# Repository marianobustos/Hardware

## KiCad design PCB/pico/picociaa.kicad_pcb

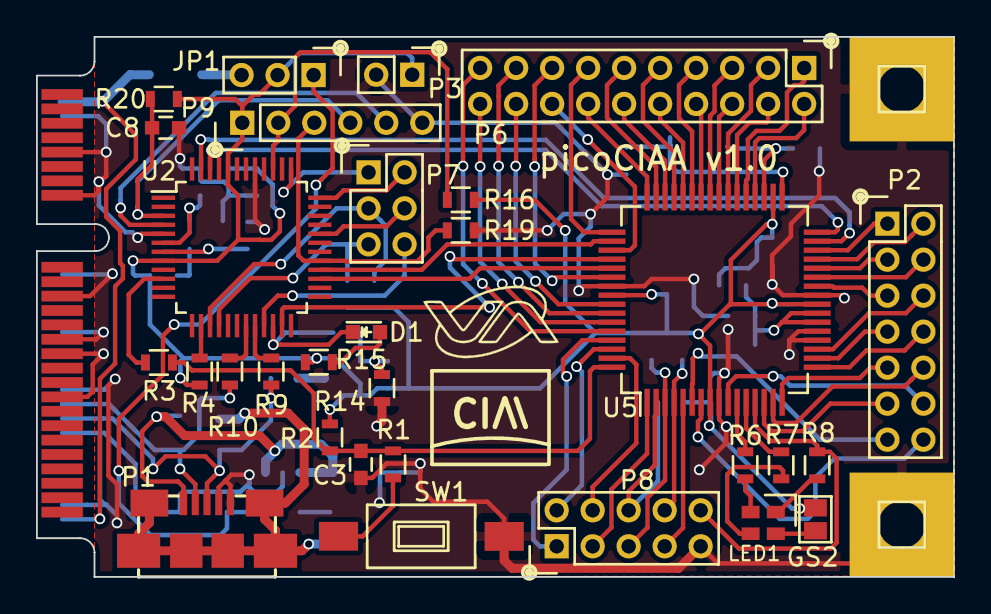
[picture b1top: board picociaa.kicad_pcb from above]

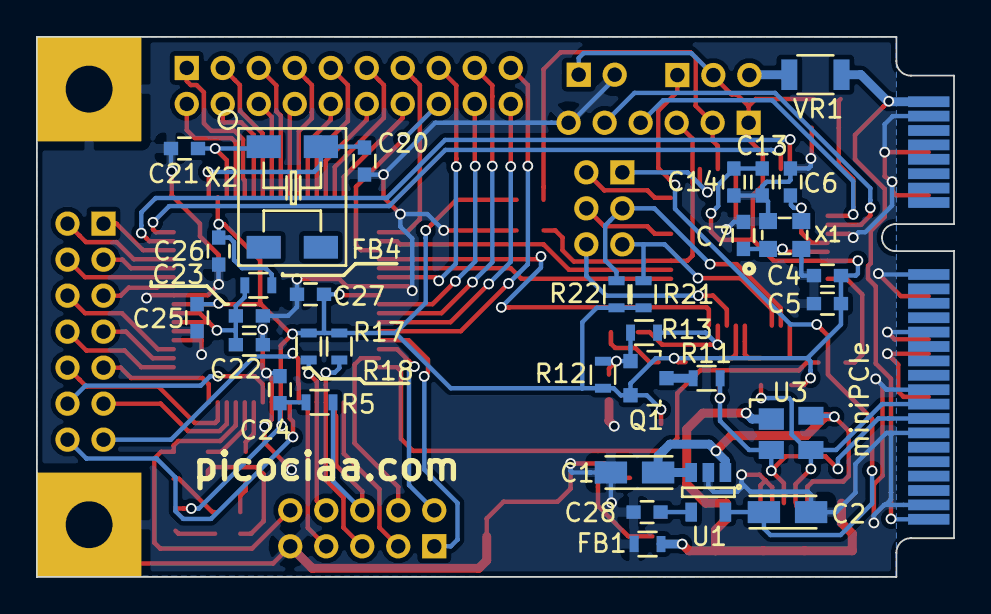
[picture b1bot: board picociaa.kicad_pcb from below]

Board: 2 copper layers, 51.0 x 30.0 mm, 66 parts (33 on the bottom side), 89 nets.

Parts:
C1, C2: 10uF; TantalC_SizeA_EIA-3216_Reflow
C3, C4, C8, C13, C23, C24, C25, C26, C27: 100nF; C_0603
C5, C14, C22, C28: 10nF; C_0603
C6, C7: 18pF; C_0603
C20, C21: 20pF; C_0603
D1: LED; LED_0603
FB1, FB4: FILTER; R_0603
GS2: GS2
J1: PCIE-MINI; miniPCIeConn
JP1: VDD Sel.; Pin_Header_Straight_1x03_Pitch2.00mm
LED1: LTST-C19FD1WT; PLCC-4
P1: ZX62D-B-5P8; USB_microAB_ZX62-AB&B-5PA-11
P2: IO2; Pin_Header_Straight_2x07_Pitch2.00mm
P3: PWR; Pin_Header_Straight_1x02_Pitch2.00mm
P4, P5: MOUNTING_HOLE; PIN_ARRAY_1
P6: IO1; Pin_Header_Straight_2x10_Pitch2.00mm
P7: DBG_IO; Pin_Header_Straight_2x03_Pitch2.00mm
P8: IO3; Pin_Header_Straight_2x05_Pitch2.00mm
P9: DBG_SWD; Pin_Header_Straight_1x06_Pitch2.00mm
Q1: BC857; SOT-23
R1, R3: 100; R_0603
R2, R5: 100k; R_0603
R4, R13, R15, R21, R22: 2k; R_0603
R6, R7: 270; R_0603
R8, R11: 1.5k; R_0603
R9, R10: 33; R_0603
R12, R16, R19: 24k; R_0603
R14: UL; R_0603
R17, R18: 2.2k; R_0603
R20: 10k; R_0603
SW1: RESET; SW_SPST_FSMSM
U1: MIC5319-3.3YD5; SOT-23-5
U2: LPC11U35FBD48; LQFP-48_7x7mm_Pitch0.5mm
U3: PRTR5V0U2X; SOT-143
U5: LPC54102J512BD64; TQFP-64_10x10mm_Pitch0.5mm
VR1: VR; R_1206
X1: 12MHz; FA238V-XTAL
X2: 32.768kHz; 4SOJ

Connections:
+3V3: C4.1, C5.1, C13.1, C14.1, C24.1, C25.1, C26.1, C27.1, FB4.2, GS2.2, JP1.2, P3.1, P9.1, Q1.2, R2.1, R4.2, R5.1, R12.1, R15.1, R16.1, R17.2, R18.2, R20.1, R21.2, R22.2, U2.8, U2.44, U5.8, U5.24, U5.34, U5.56
/CHASSIS: FB1.1, P1.6, P1.7, P1.8, P1.9, U3.1
/Debugger/DBG_SWCLK: P9.3, R19.1, U2.29
/Debugger/DBG_SWDIO: P9.2, R16.2, U2.39
/Debugger/DBG_~ISP~: P9.5, U2.4
/Debugger/DBG_~RST~: C8.1, P9.4, R20.2, U2.3
/Debugger/PIO0_4: P7.3, R22.1, U2.15
/Debugger/PIO0_5: P7.5, R21.1, U2.16
/Debugger/PIO0_11: P7.4, U2.32
/Debugger/PIO1_13: P7.2, U2.36
/Debugger/PIO1_14: P7.1, U2.37
/Debugger/PIO1_24: P7.6, U2.21
/Debugger/TGT_TXD: U2.46, U5.32
/Debugger/TGT_~RESET~: C3.1, R1.2, R2.2, R3.2, U5.64
/Debugger/USB_N: J1.36, P1.2, R10.1, U3.3
/Debugger/USB_P: J1.38, P1.3, R9.1, R11.1, U3.2
/Debugger/~USB_CONNECT~: D1.1, R13.2, U2.22
/PCIe_3.3V: JP1.3, VR1.1
/Reg_3.3V: C2.1, JP1.1, U1.5
/Target CPU/P0_2: P6.2, U5.36
/Target CPU/P0_3: P6.1, U5.37
/Target CPU/P0_4: P6.4, U5.38
/Target CPU/P0_5: P6.3, U5.39
/Target CPU/P0_6: P6.6, U5.40
/Target CPU/P0_7: P6.5, U5.41
/Target CPU/P0_8: P6.7, U5.43
/Target CPU/P0_9: P6.10, U5.44
/Target CPU/P0_10: P6.9, U5.45
/Target CPU/P0_11: P6.12, U5.46
/Target CPU/P0_12: P6.11, U5.47
/Target CPU/P0_13: P6.14, U5.48
/Target CPU/P0_14: P6.13, U5.49
/Target CPU/P0_18: P6.17, U5.58
/Target CPU/P0_19: P6.20, U5.59
/Target CPU/P0_20: P6.19, U5.60
/Target CPU/P0_21: P8.1, U5.61
/Target CPU/P0_22: P8.4, U5.63
/Target CPU/P0_23: P8.3, U5.1
/Target CPU/P0_24: P8.6, R5.2, U5.2
/Target CPU/P0_25: P8.5, R17.1, U5.3
/Target CPU/P0_26: P8.8, R18.1, U5.4
/Target CPU/P0_27: P8.7, U5.5
/Target CPU/P0_28: P2.13, U5.6
/Target CPU/P0_29: R6.2, U5.11
/Target CPU/P0_30: R7.2, U5.12
/Target CPU/P0_31: P8.10, R8.2, U5.13
/Target CPU/P1_0: P2.11, U5.14
/Target CPU/P1_1: P2.10, U5.15
/Target CPU/P1_2: P2.9, U5.16
/Target CPU/P1_3: P2.8, U5.17
/Target CPU/P1_4: P2.7, U5.18
/Target CPU/P1_5: P2.6, U5.19
/Target CPU/P1_6: P2.5, U5.26
/Target CPU/P1_7: P2.4, U5.27
/Target CPU/P1_8: P2.3, U5.28
/Target CPU/P1_9: P2.2, U5.29
/Target CPU/P1_10: P2.1, U5.30
/Target CPU/P1_11: P6.8, U5.42
/Target CPU/P1_12: P6.16, U5.51
/Target CPU/P1_13: P6.15, U5.54
/Target CPU/P1_14: P6.18, U5.57
/Target CPU/P1_15: P8.2, U5.62
/Target CPU/P1_16: P2.14, U5.7
/Target CPU/P1_17: P2.12, U5.10
/Target CPU/RXD: U2.47, U5.31
/Target CPU/SWCLK: U2.23, U5.52
/Target CPU/SWDIO: U2.27, U5.53
/Target CPU/SWO/TDO: U2.28, U5.50
/VBUS: C1.1, P1.1, U1.1, U1.3, U3.4
GND: C1.2, C2.2, C3.2, C4.2, C5.2, C6.2, C7.2, C8.2, C13.2, C14.2, C20.2, C21.2, C22.2, C23.2, C24.2, C25.2, C26.2, C27.2, C28.2, FB1.2, J1.4, J1.9, J1.15, J1.18, J1.21, J1.26, J1.27, J1.29, J1.34, J1.35, J1.40, J1.50, P1.4, P1.5, P3.2, P4.1, P5.1, P8.9, P9.6, R14.2, R19.2, SW1.1, U1.2, U2.5, U2.41, U5.9, U5.20, U5.21, U5.25, U5.55, X1.2, X1.4
unnamed: C6.1, U2.6, X1.3
unnamed: C7.1, U2.7, X1.1
unnamed: C20.1, U5.33, X2.2
unnamed: C21.1, U5.35, X2.1
unnamed: C22.1, C23.1, FB4.1, U5.22, U5.23
unnamed: C28.1, U1.4
unnamed: D1.2, R15.2
unnamed: GS2.1, LED1.4
unnamed: J1.2, J1.52, VR1.2
unnamed: LED1.1, R8.1
unnamed: LED1.2, R6.1
unnamed: LED1.3, R7.1
unnamed: Q1.1, R12.2, R13.1, R14.1
unnamed: Q1.3, R11.2
unnamed: R1.1, SW1.2
unnamed: R3.1, U2.10
unnamed: R4.1, U2.14
unnamed: R9.2, U2.20
unnamed: R10.2, U2.19

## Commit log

2017-03-12 Actualización de modelos 3D
    Se actualizaron los modelos 3D. Falta actualizar la libreria y las rutas
    relativas.
